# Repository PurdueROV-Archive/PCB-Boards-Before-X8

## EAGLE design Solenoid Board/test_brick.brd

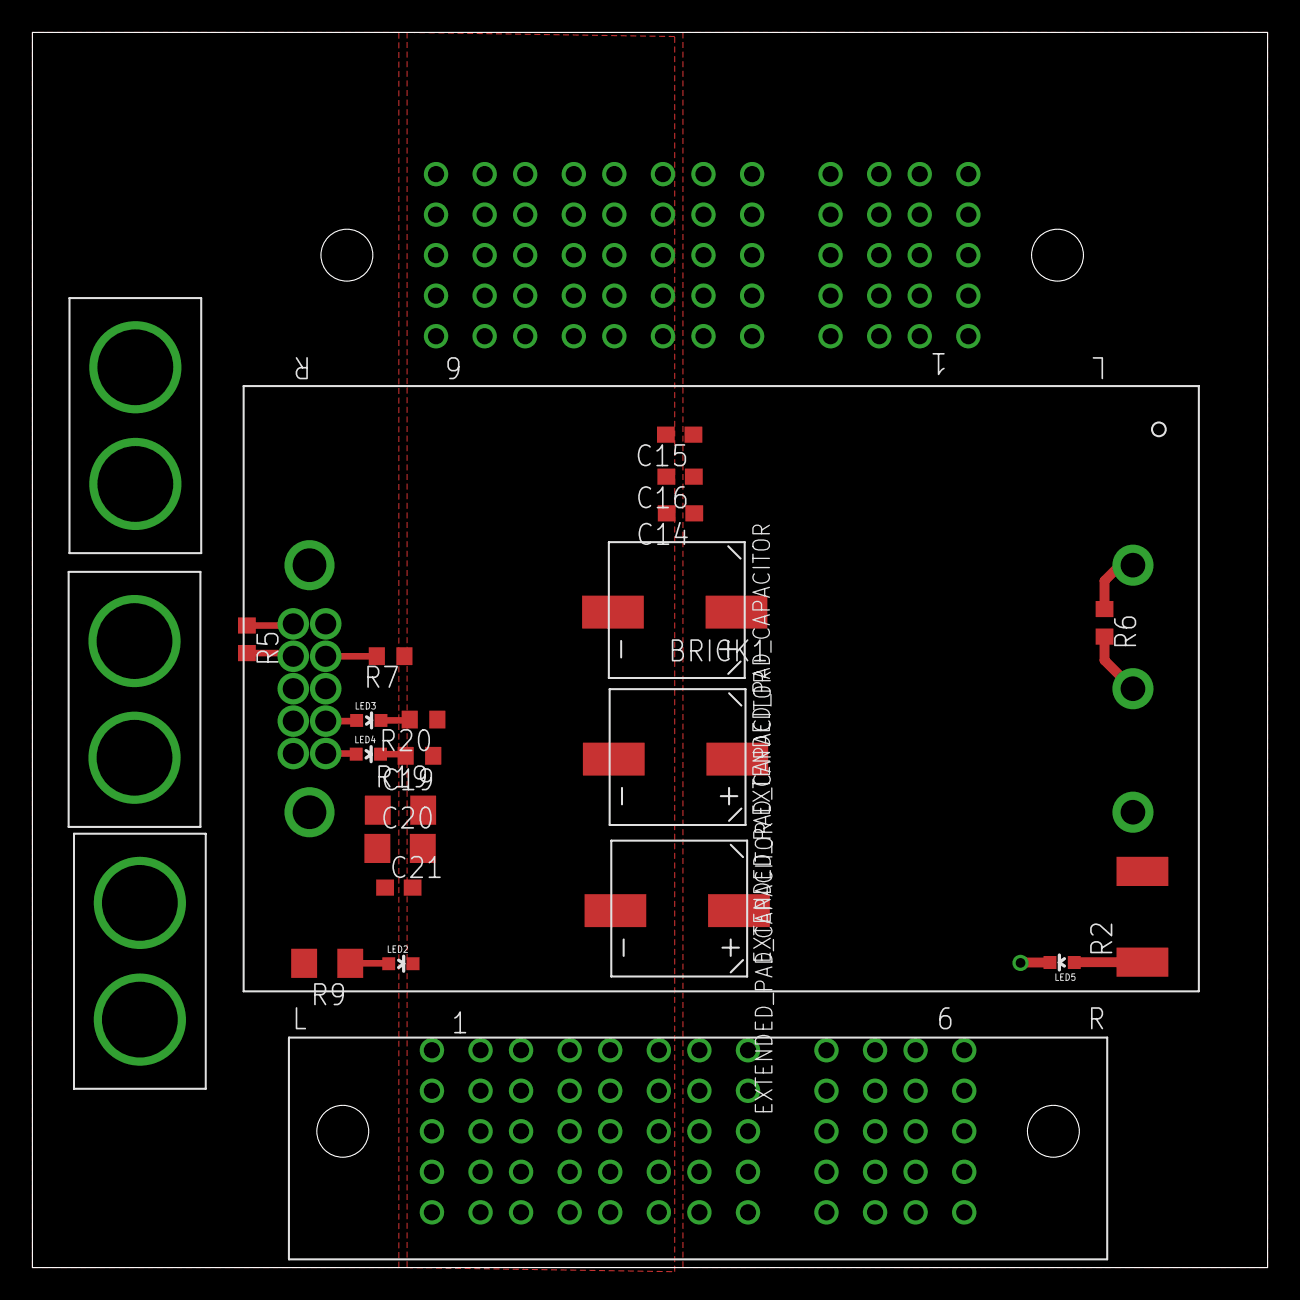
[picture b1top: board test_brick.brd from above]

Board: 2 copper layers, 76.2 x 76.2 mm, 26 parts (0 on the bottom side), 12 nets.

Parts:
BRICK1: BRICK_DC-DC_CONVERTER
C14, C15, C16: .1uF; C0603
C19, C20: 15uF; C3216
C21: 10uF; C0603
C22V1, C22V5, C22V6: EXTENDED_PAD_CAPACITOR; MODIFIED-NICHICON-UX-8X10
LED2, LED3, LED5: GREEN; LED-0603
LED4: RED; LED-0603
R2: 2700; R2512
R5, R7: 10k; R0603
R6: 0; R0603
R9: 1.1k; R1206
R19, R20: 1k; R0603
U$1: ET60S-04-00-02-L-RT1-GP
U$2, U$3, U$10: XT60
U$4: ET60T-04-00-02-L-RT1-GP

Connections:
+12V1: BRICK1.6, BRICK1.16, C19.1, C20.1, C21.1, R9.2, U$2.P$2, U$3.P$2, U$10.P$2
+48V: BRICK1.1, C14.1, C15.1, C16.1, C22V1.P$3, C22V5.P$3, C22V6.P$3, R2.2, U$1.P6.1, U$1.P6.2, U$1.P6.3, U$1.P6.4, U$1.P6.5, U$1.P6.6, U$1.P6.7, U$1.P6.8, U$1.P6.9, U$1.P6.10, U$1.P7.1, U$1.P7.2, U$1.P7.3, U$1.P7.4, U$1.P7.5, U$1.P7.6, U$1.P7.7, U$1.P7.8, U$1.P7.9, U$1.P7.10, U$1.P8.1, U$1.P8.2, U$1.P8.3, U$1.P8.4, U$1.P8.5, U$1.P8.6, U$1.P8.7, U$1.P8.8, U$1.P8.9, U$1.P8.10, U$4.P6.1, U$4.P6.2, U$4.P6.3, U$4.P6.4, U$4.P6.5, U$4.P6.6, U$4.P6.7, U$4.P6.8, U$4.P6.9, U$4.P6.10, U$4.P7.1, U$4.P7.2, U$4.P7.3, U$4.P7.4, U$4.P7.5, U$4.P7.6, U$4.P7.7, U$4.P7.8, U$4.P7.9, U$4.P7.10, U$4.P8.1, U$4.P8.2, U$4.P8.3, U$4.P8.4, U$4.P8.5, U$4.P8.6, U$4.P8.7, U$4.P8.8, U$4.P8.9, U$4.P8.10
ADRS00A: BRICK1.8, R7.2
ADRS00B: BRICK1.9, R5.2
ALERT: BRICK1.14, LED4.A
GND: BRICK1.4, BRICK1.5, BRICK1.7, C14.2, C15.2, C16.2, C19.2, C20.2, C21.2, C22V1.P$1, C22V5.P$1, C22V6.P$1, LED2.C, LED5.C, R5.1, R6.1, R7.1, R19.1, R20.1, U$1.P3.1, U$1.P3.2, U$1.P3.3, U$1.P3.4, U$1.P3.5, U$1.P3.6, U$1.P3.7, U$1.P3.8, U$1.P3.9, U$1.P3.10, U$1.P4.1, U$1.P4.2, U$1.P4.3, U$1.P4.4, U$1.P4.5, U$1.P4.6, U$1.P4.7, U$1.P4.8, U$1.P4.9, U$1.P4.10, U$1.P5.1, U$1.P5.2, U$1.P5.3, U$1.P5.4, U$1.P5.5, U$1.P5.6, U$1.P5.7, U$1.P5.8, U$1.P5.9, U$1.P5.10, U$2.P$1, U$3.P$1, U$4.P3.1, U$4.P3.2, U$4.P3.3, U$4.P3.4, U$4.P3.5, U$4.P3.6, U$4.P3.7, U$4.P3.8, U$4.P3.9, U$4.P3.10, U$4.P4.1, U$4.P4.2, U$4.P4.3, U$4.P4.4, U$4.P4.5, U$4.P4.6, U$4.P4.7, U$4.P4.8, U$4.P4.9, U$4.P4.10, U$4.P5.1, U$4.P5.2, U$4.P5.3, U$4.P5.4, U$4.P5.5, U$4.P5.6, U$4.P5.7, U$4.P5.8, U$4.P5.9, U$4.P5.10, U$10.P$1
unnamed: BRICK1.2, R6.2
unnamed: LED5.A, R2.1
unnamed: LED4.C, R19.2
unnamed: LED3.C, R20.2
unnamed: LED2.A, R9.1
PG: BRICK1.12, LED3.A

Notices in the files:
parts and their libraries:
SparkFun: Licensing: CC v3.0 Share-Alike You are welcome to use this library for commercial purposes.
